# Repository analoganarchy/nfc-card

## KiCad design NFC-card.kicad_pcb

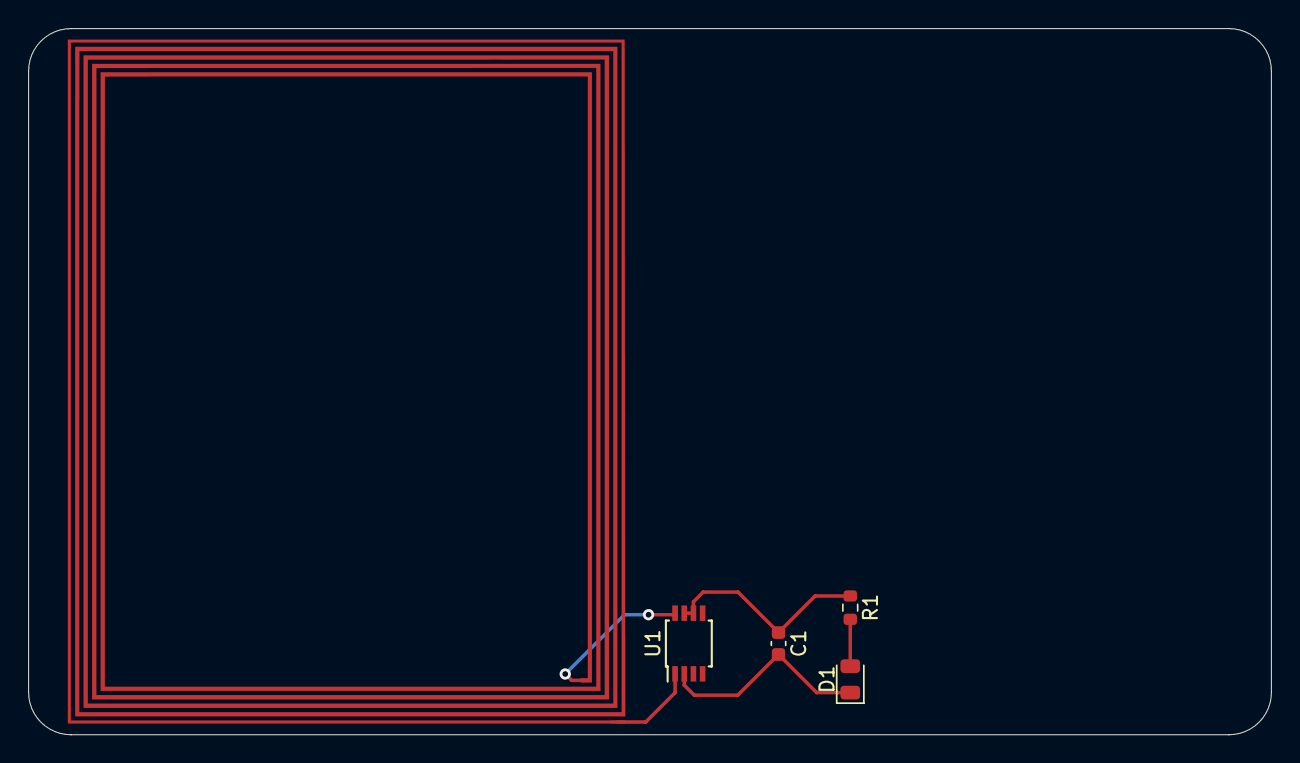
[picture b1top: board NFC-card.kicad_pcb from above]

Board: 2 copper layers, 88.0 x 50.0 mm, 5 parts (0 on the bottom side), 5 nets.

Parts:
C1: 0.22uF; C_0603_1608Metric
D1: LED; LED_0805_2012Metric
L1: NFC_ANT; antenna
R1: 47; R_0603_1608Metric
U1: NT3H2111; TSSOP-8_3x3mm_P0.65mm

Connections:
unnamed: C1.1, R1.1, U1.6, U1.7
unnamed: C1.2, D1.1, U1.2
unnamed: D1.2, R1.2
unnamed: L1.1, U1.8
unnamed: L1.2, U1.1

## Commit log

2021-12-14 initial
2021-12-15 Added License
2021-12-20 added ignore
2021-12-20 updated ignore
2021-12-20 removed netlist
2021-12-20 organized
